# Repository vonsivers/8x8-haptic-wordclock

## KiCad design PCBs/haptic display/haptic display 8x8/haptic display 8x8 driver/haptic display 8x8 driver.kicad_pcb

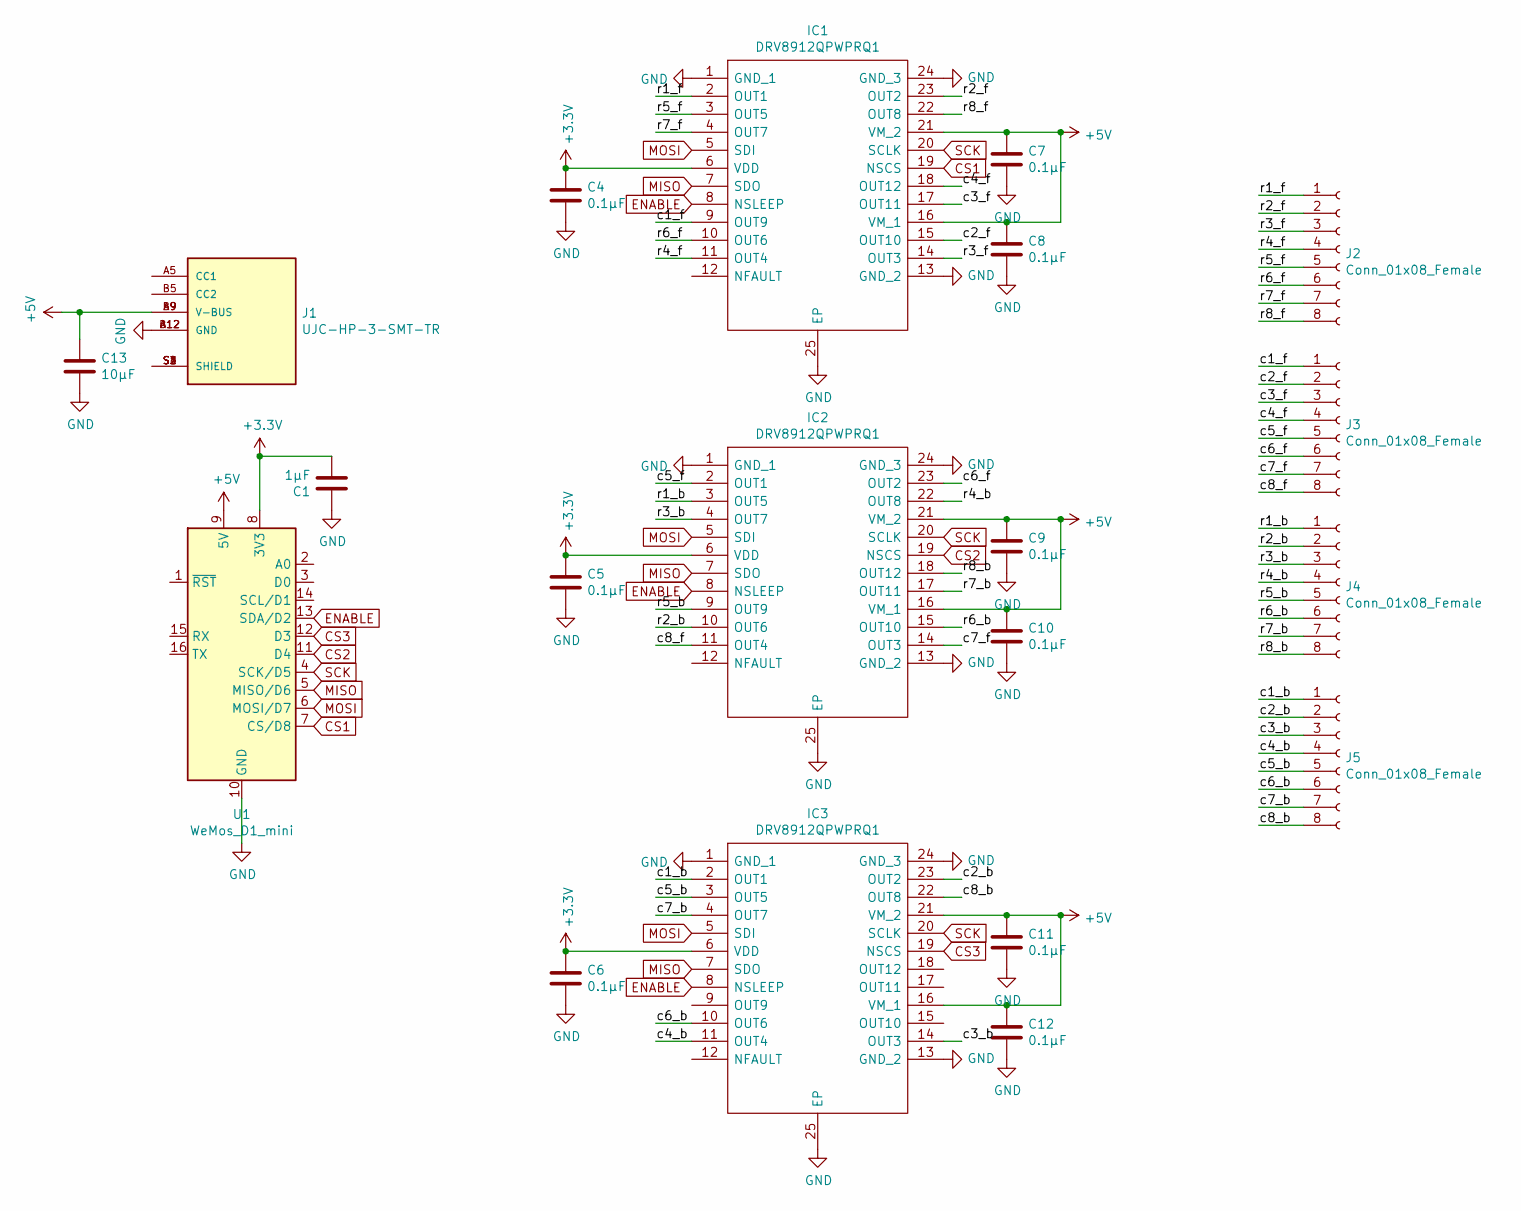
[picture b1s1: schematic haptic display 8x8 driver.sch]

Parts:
C1: 1µF; C_0805_2012Metric
C4, C5, C6, C7, C8, C9, C10, C11, C12: 0.1µF; C_0805_2012Metric
C13: 10µF; C_1210_3225Metric
IC1, IC2, IC3: DRV8912QPWPRQ1; SOP65P640X120-25N; Mouser Part Number 595-DRV8912QPWPRQ1
J1: UJC-HP-3-SMT-TR; CUI_UJC-HP-3-SMT-TR; PARTREV 1.0
J2, J3, J4, J5: Conn_01x08_Female; PinSocket_1x08_P2.54mm_Vertical
U1: WeMos_D1_mini; WEMOS_D1_mini_light

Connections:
+3V3: C1.2, C4.1, C5.1, C6.1, IC1.6 (VDD), IC2.6 (VDD), IC3.6 (VDD), U1.8 (3V3)
+5V: C7.1, C8.1, C9.1, C10.1, C11.1, C12.1, C13.1, IC1.16 (VM_1), IC1.21 (VM_2), IC2.16 (VM_1), IC2.21 (VM_2), IC3.16 (VM_1), IC3.21 (VM_2), J1.A9 (V-BUS), J1.B9 (V-BUS), U1.9 (5V)
/c1_b: IC3.2 (OUT1), J5.1
/c1_f: IC1.9 (OUT9), J3.1
/c2_b: IC3.23 (OUT2), J5.2
/c2_f: IC1.15 (OUT10), J3.2
/c3_b: IC3.14 (OUT3), J5.3
/c3_f: IC1.17 (OUT11), J3.3
/c4_b: IC3.11 (OUT4), J5.4
/c4_f: IC1.18 (OUT12), J3.4
/c5_b: IC3.3 (OUT5), J5.5
/c5_f: IC2.2 (OUT1), J3.5
/c6_b: IC3.10 (OUT6), J5.6
/c6_f: IC2.23 (OUT2), J3.6
/c7_b: IC3.4 (OUT7), J5.7
/c7_f: IC2.14 (OUT3), J3.7
/c8_b: IC3.22 (OUT8), J5.8
/c8_f: IC2.11 (OUT4), J3.8
/r1_b: IC2.3 (OUT5), J4.1
/r1_f: IC1.2 (OUT1), J2.1
/r2_b: IC2.10 (OUT6), J4.2
/r2_f: IC1.23 (OUT2), J2.2
/r3_b: IC2.4 (OUT7), J4.3
/r3_f: IC1.14 (OUT3), J2.3
/r4_b: IC2.22 (OUT8), J4.4
/r4_f: IC1.11 (OUT4), J2.4
/r5_b: IC2.9 (OUT9), J4.5
/r5_f: IC1.3 (OUT5), J2.5
/r6_b: IC2.15 (OUT10), J4.6
/r6_f: IC1.10 (OUT6), J2.6
/r7_b: IC2.17 (OUT11), J4.7
/r7_f: IC1.4 (OUT7), J2.7
/r8_b: IC2.18 (OUT12), J4.8
/r8_f: IC1.22 (OUT8), J2.8
CS1: IC1.19 (NSCS), U1.7 (CS/D8)
CS2: IC2.19 (NSCS), U1.11 (D4)
CS3: IC3.19 (NSCS), U1.12 (D3)
ENABLE: IC1.8 (NSLEEP), IC2.8 (NSLEEP), IC3.8 (NSLEEP), U1.13 (SDA/D2)
GND: C1.1, C4.2, C5.2, C6.2, C7.2, C8.2, C9.2, C10.2, C11.2, C12.2, C13.2, IC1.1 (GND_1), IC1.13 (GND_2), IC1.24 (GND_3), IC1.25 (EP), IC2.1 (GND_1), IC2.13 (GND_2), IC2.24 (GND_3), IC2.25 (EP), IC3.1 (GND_1), IC3.13 (GND_2), IC3.24 (GND_3), IC3.25 (EP), J1.A12 (GND), J1.B12 (GND), U1.10 (GND)
MISO: IC1.7 (SDO), IC2.7 (SDO), IC3.7 (SDO), U1.5 (MISO/D6)
MOSI: IC1.5 (SDI), IC2.5 (SDI), IC3.5 (SDI), U1.6 (MOSI/D7)
unnamed: J1.S1 (SHIELD), J1.S2 (SHIELD), J1.S3 (SHIELD), J1.S4 (SHIELD)
SCK: IC1.20 (SCLK), IC2.20 (SCLK), IC3.20 (SCLK), U1.4 (SCK/D5)

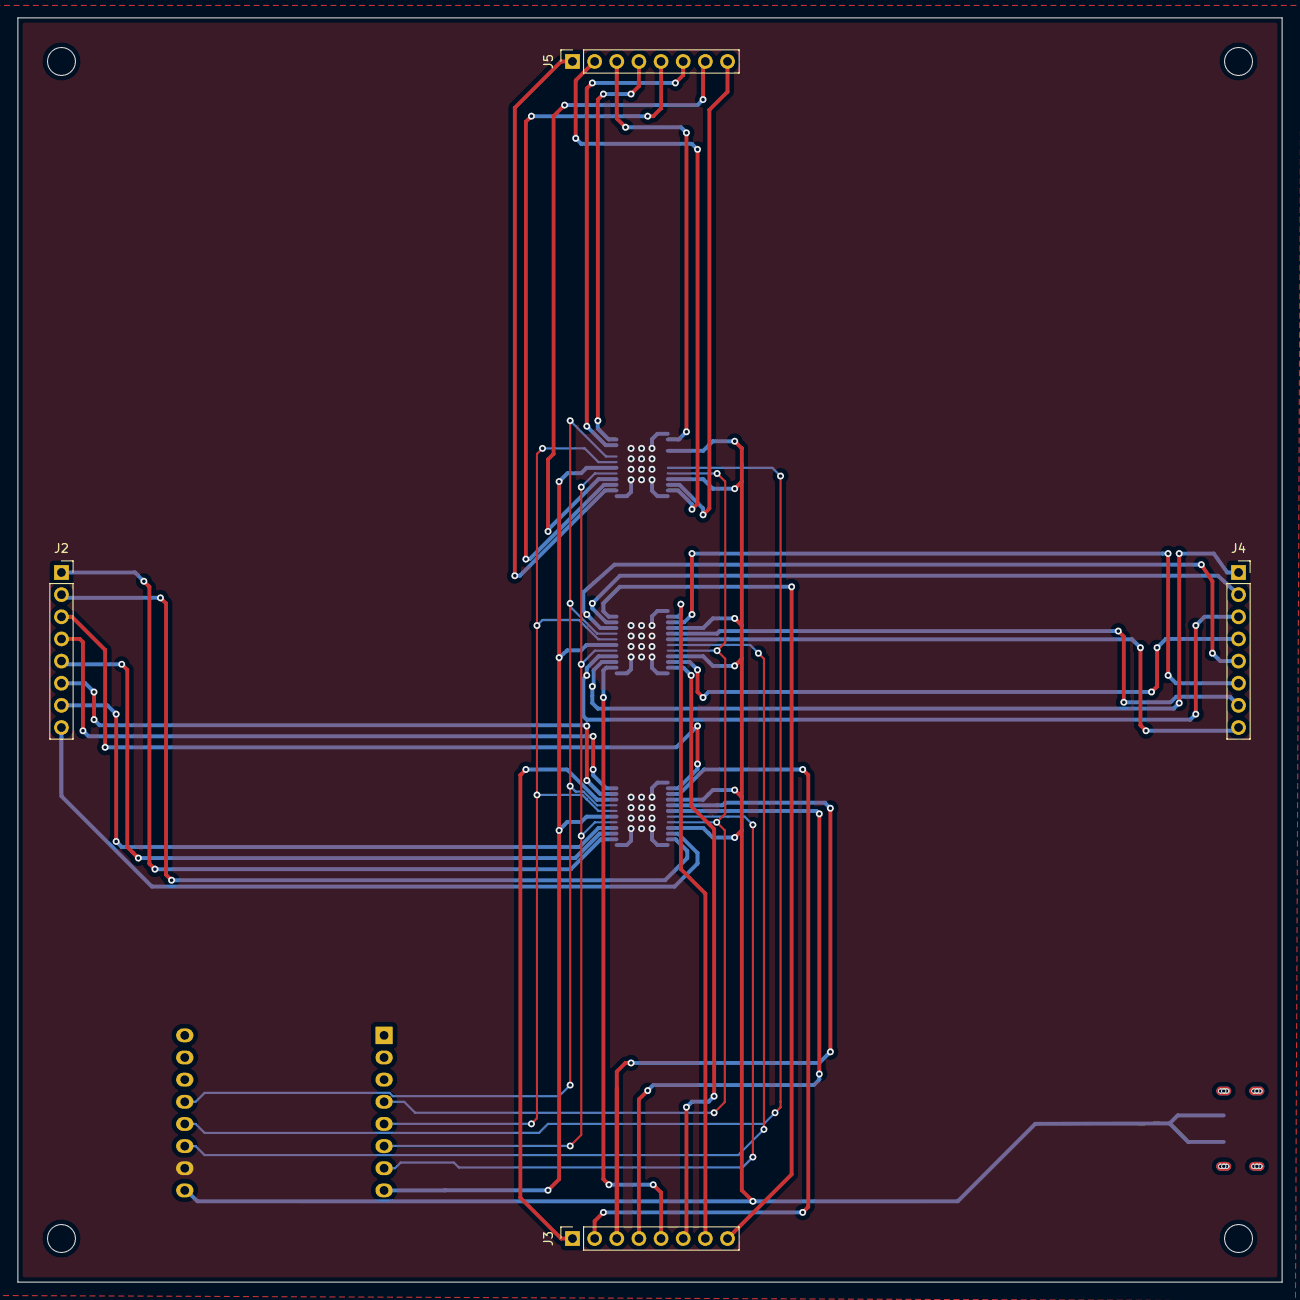
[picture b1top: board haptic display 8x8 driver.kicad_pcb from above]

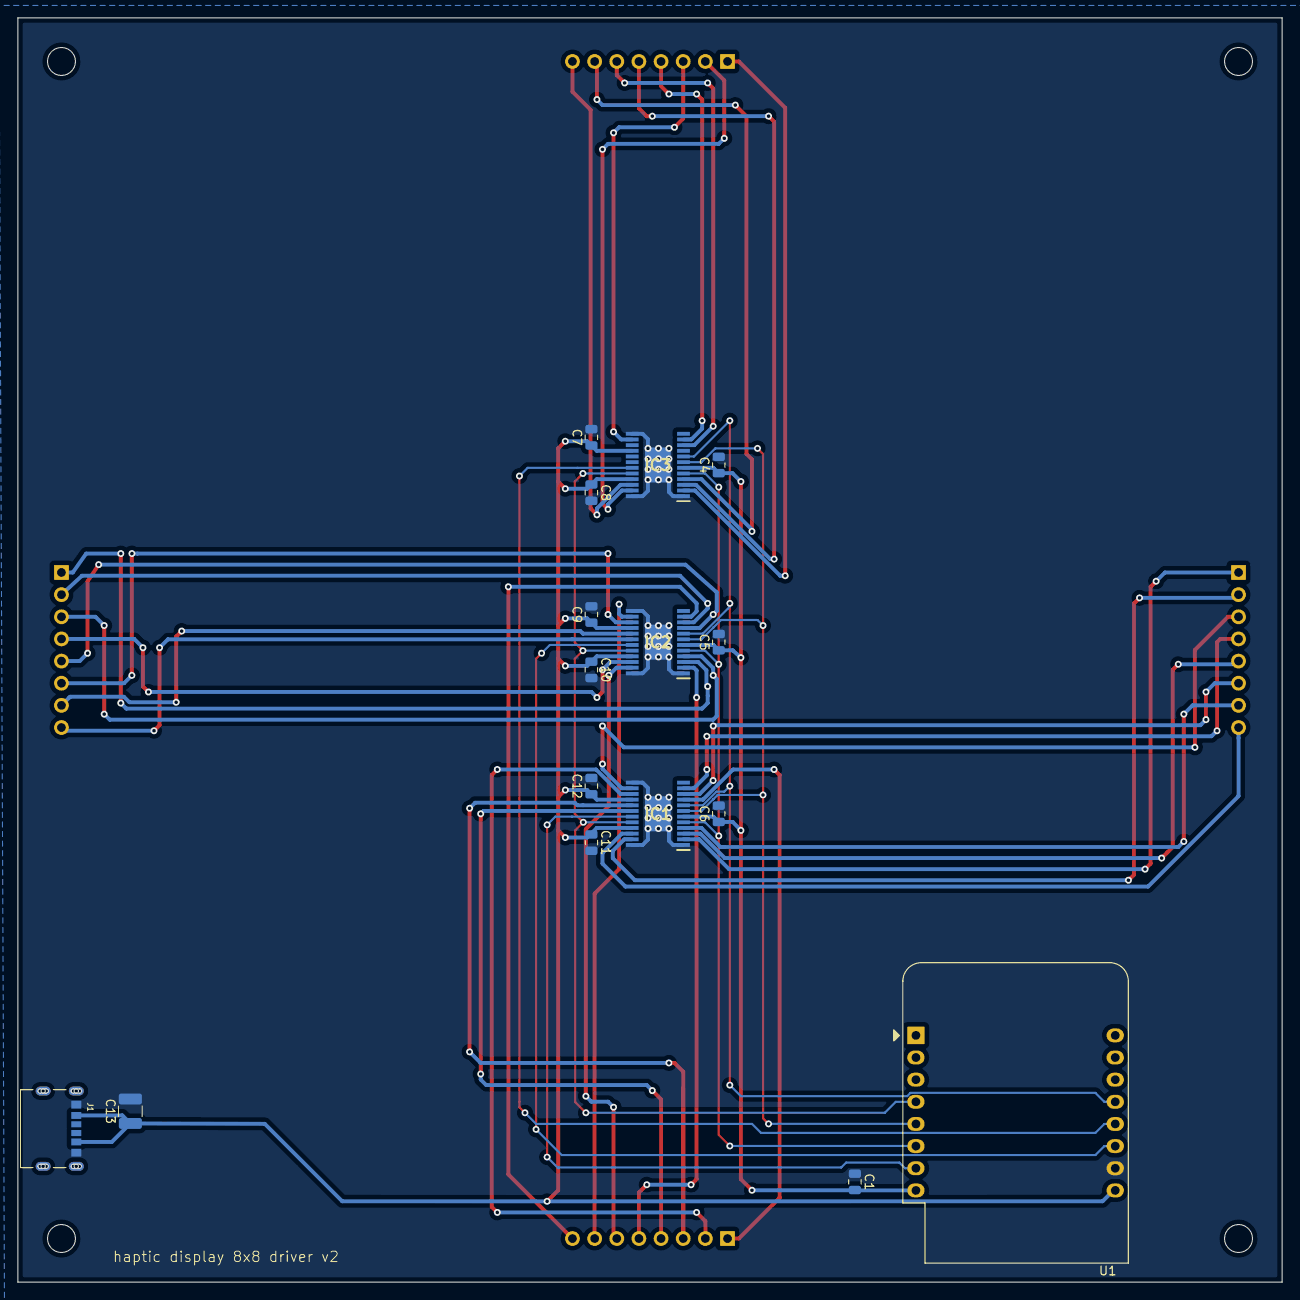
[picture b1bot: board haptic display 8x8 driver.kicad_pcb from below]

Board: 2 copper layers, 145.0 x 145.0 mm, 20 parts (16 on the bottom side), 43 nets.

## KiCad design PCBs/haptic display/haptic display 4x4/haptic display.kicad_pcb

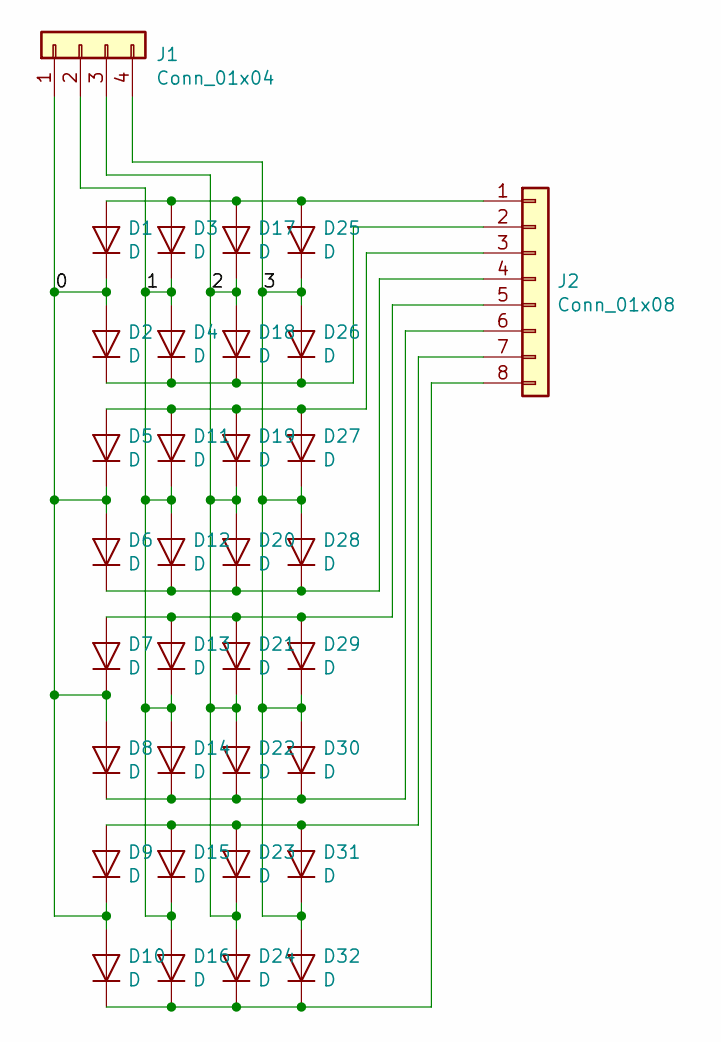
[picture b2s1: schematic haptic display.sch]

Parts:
D1, D2, D3, D4, D5, D6, D7, D8, D9, D10, D11, D12, D13, D14, D15, D16, D17, D18, D19, D20, D21, D22, D23, D24, D25, D26, D27, D28, D29, D30, D31, D32: D; D_0805_2012Metric
J1: Conn_01x04; PinSocket_1x04_P2.54mm_Vertical
J2: Conn_01x08; PinSocket_1x08_P2.54mm_Vertical

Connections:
/0: D1.1 (K), D2.2 (A), D5.1 (K), D6.2 (A), D7.1 (K), D8.2 (A), D9.1 (K), D10.2 (A), J1.1
/1: D3.1 (K), D4.2 (A), D11.1 (K), D12.2 (A), D13.1 (K), D14.2 (A), D15.1 (K), D16.2 (A), J1.2
/2: D17.1 (K), D18.2 (A), D19.1 (K), D20.2 (A), D21.1 (K), D22.2 (A), D23.1 (K), D24.2 (A), J1.3
/3: D25.1 (K), D26.2 (A), D27.1 (K), D28.2 (A), D29.1 (K), D30.2 (A), D31.1 (K), D32.2 (A), J1.4
unnamed: D1.2 (A), D3.2 (A), D17.2 (A), D25.2 (A), J2.1
unnamed: D10.1 (K), D16.1 (K), D24.1 (K), D32.1 (K), J2.8
unnamed: D5.2 (A), D11.2 (A), D19.2 (A), D27.2 (A), J2.3
unnamed: D6.1 (K), D12.1 (K), D20.1 (K), D28.1 (K), J2.4
unnamed: D7.2 (A), D13.2 (A), D21.2 (A), D29.2 (A), J2.5
unnamed: D8.1 (K), D14.1 (K), D22.1 (K), D30.1 (K), J2.6
unnamed: D9.2 (A), D15.2 (A), D23.2 (A), D31.2 (A), J2.7
unnamed: D2.1 (K), D4.1 (K), D18.1 (K), D26.1 (K), J2.2

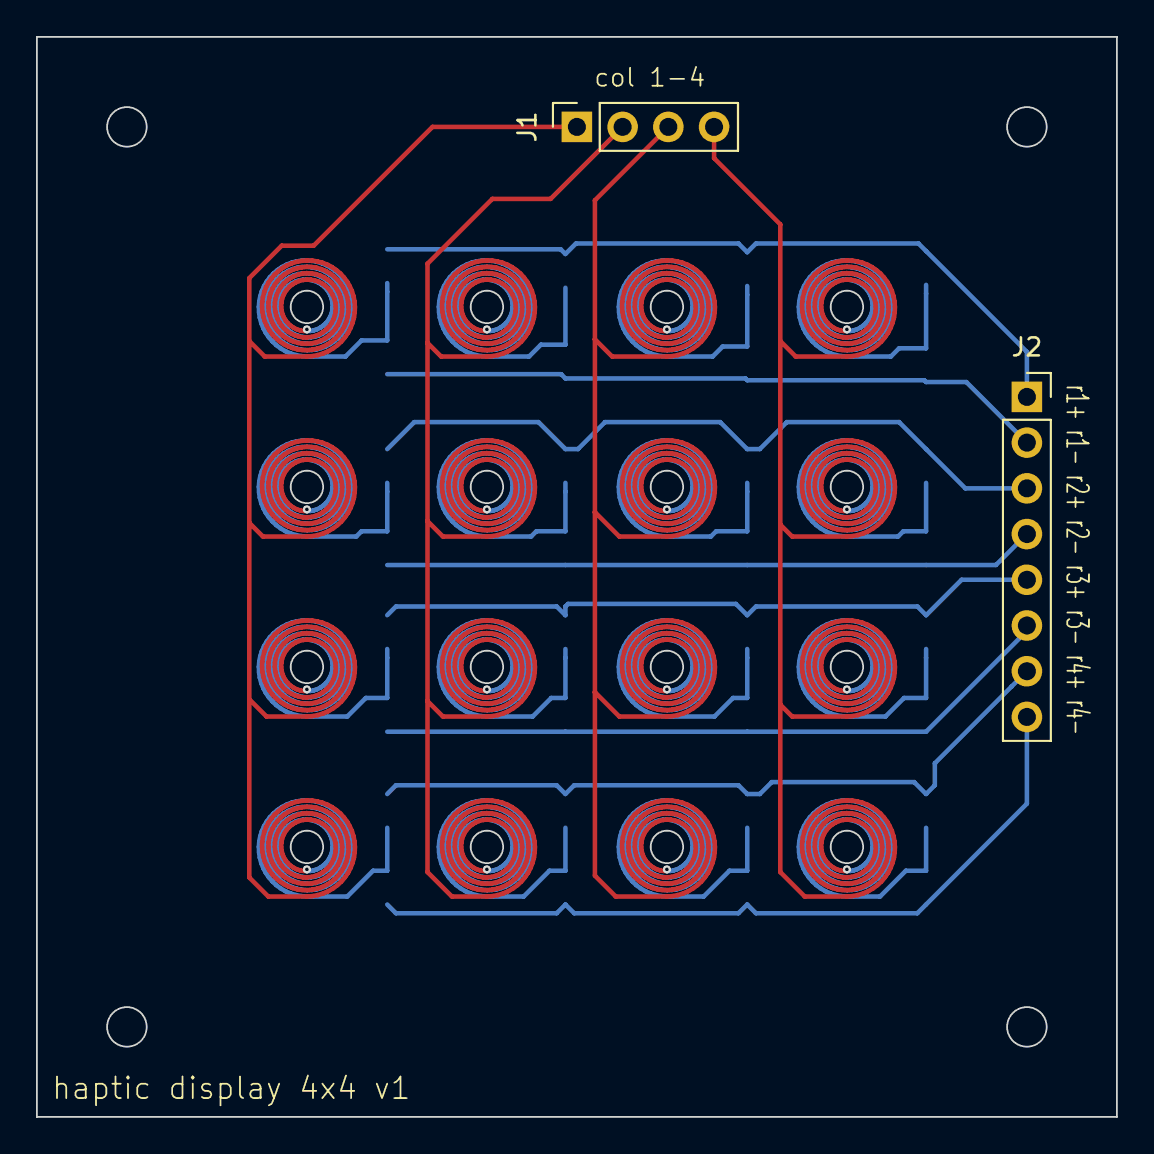
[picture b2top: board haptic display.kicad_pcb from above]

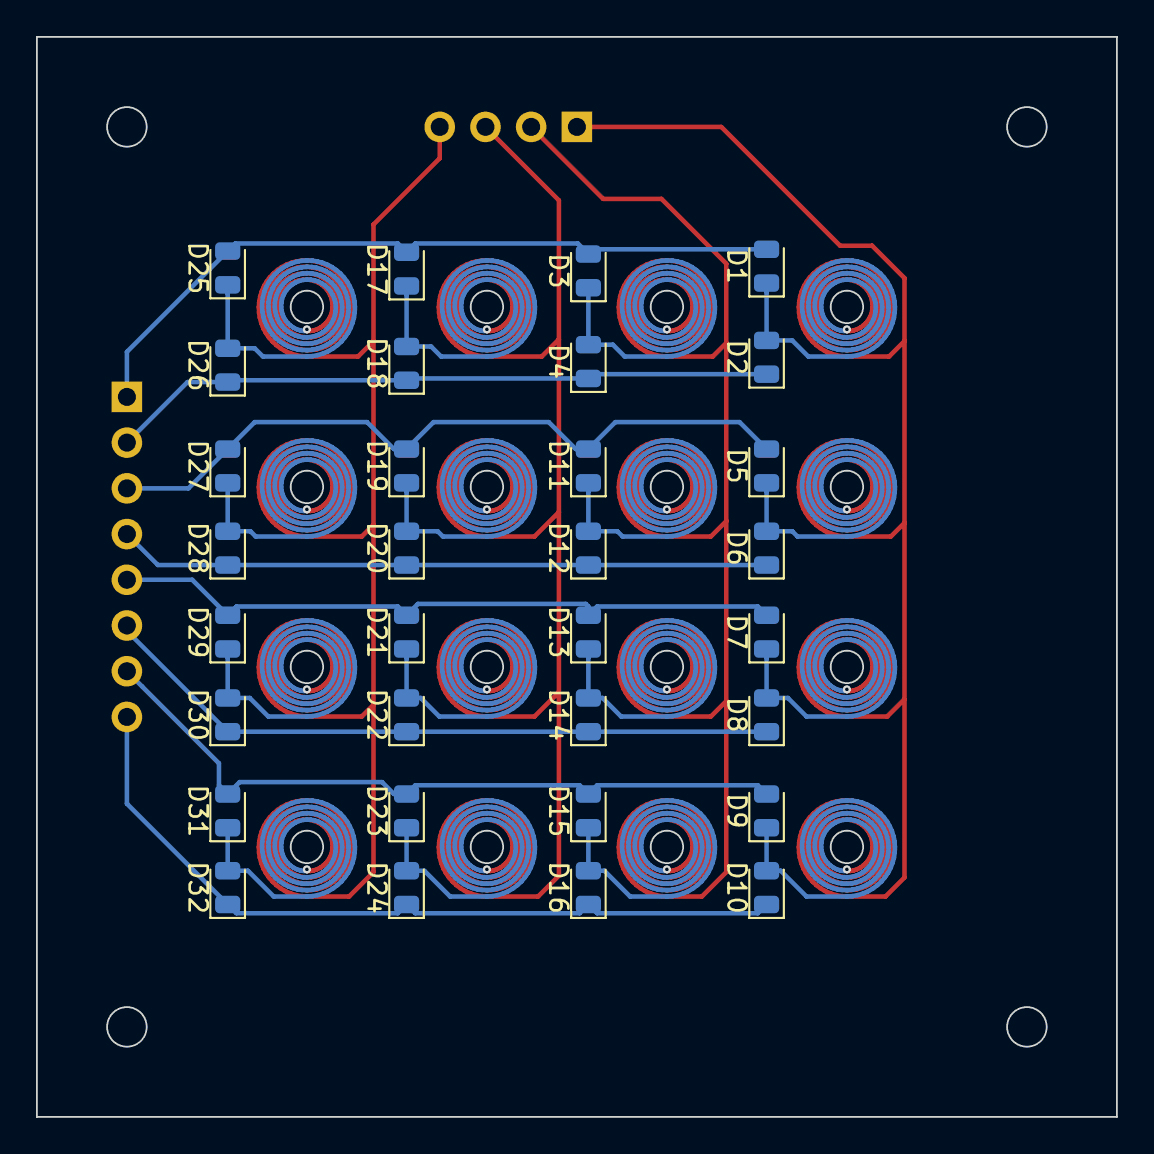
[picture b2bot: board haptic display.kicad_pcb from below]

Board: 2 copper layers, 60.0 x 60.0 mm, 34 parts (32 on the bottom side), 12 nets.

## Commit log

2021-03-28 cleanup
2021-04-09 updated tolerances on stl files
2021-04-10 Update 8x8_haptic_wordclock.ino
    use build-in NTP library, added DST support
